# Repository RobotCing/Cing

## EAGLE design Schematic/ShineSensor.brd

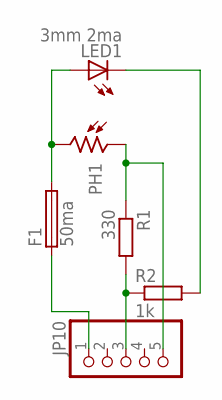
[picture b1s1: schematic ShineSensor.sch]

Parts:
F1: 50ma; MF-SMDF050
JP10: PINHD-1X5; 1X05
LED1: 3mm 2ma; LED3MM
PH1: B1060_23; TO-8_B10
R1: 330; R1206
R2: 1k; R1206

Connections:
unnamed: F1.2, LED1.A, PH1.2
unnamed: LED1.K (C), R2.2
unnamed: JP10.5, PH1.1, R1.1
unnamed: JP10.3, R1.2, R2.1
unnamed: F1.1, JP10.1

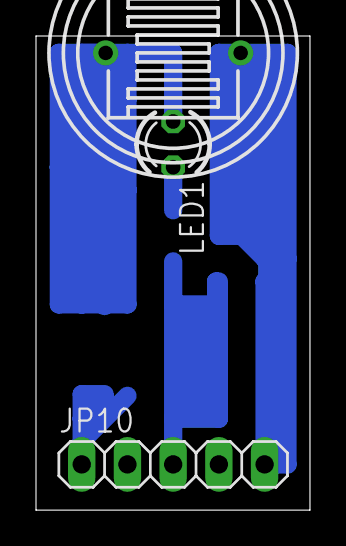
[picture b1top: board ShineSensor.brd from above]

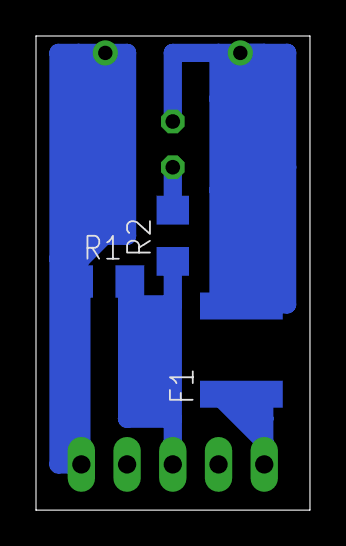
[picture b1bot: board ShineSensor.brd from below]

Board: 2 copper layers, 15.2 x 26.3 mm, 6 parts (3 on the bottom side), 5 nets.

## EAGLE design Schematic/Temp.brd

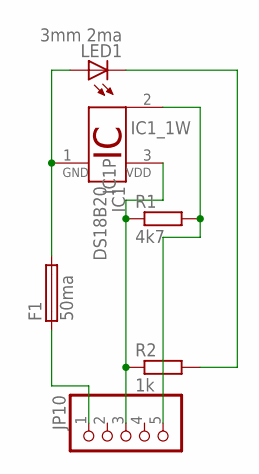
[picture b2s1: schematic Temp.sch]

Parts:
F1: 50ma; MF-SMDF050
IC1: DS18B20; TO92-
JP10: PINHD-1X5; 1X05
LED1: 3mm 2ma; LED3MM
R1: 4k7; R1206
R2: 1k; R1206

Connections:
unnamed: F1.2, IC1.1 (GND), LED1.A
unnamed: LED1.K (C), R2.2
unnamed: IC1.2 (1W), JP10.5, R1.2
unnamed: IC1.3 (VDD), JP10.3, R1.1, R2.1
unnamed: F1.1, JP10.1

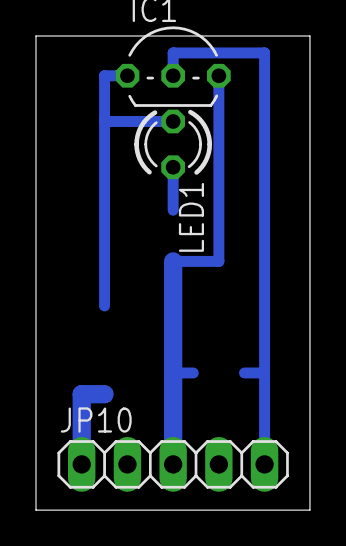
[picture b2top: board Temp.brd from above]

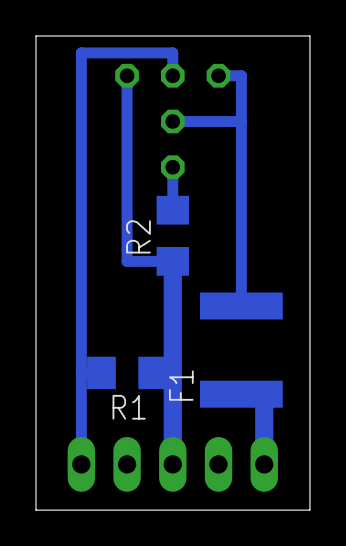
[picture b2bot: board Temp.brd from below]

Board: 2 copper layers, 15.2 x 26.3 mm, 6 parts (3 on the bottom side), 5 nets.

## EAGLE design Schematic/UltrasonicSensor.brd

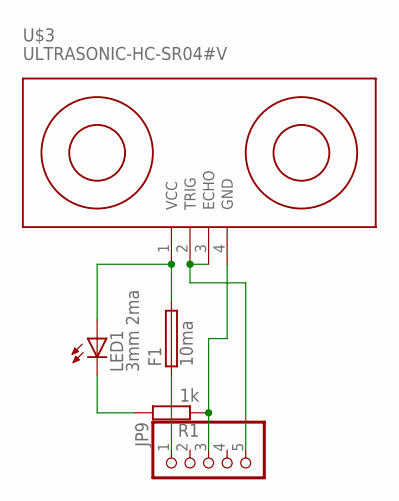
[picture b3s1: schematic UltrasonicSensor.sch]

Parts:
F1: 10ma; MF-SMDF050
JP9: PINHD-1X5; 1X05
LED1: 3mm 2ma; LED3MM
R1: 1k; M1206
U$3: ULTRASONIC-HC-SR04#V

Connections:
unnamed: JP9.3, R1.1, U$3.4 (GND)
unnamed: F1.1, JP9.1
unnamed: F1.2, LED1.A, U$3.1 (VCC)
unnamed: LED1.K (C), R1.2
unnamed: JP9.5, U$3.2 (TRIG), U$3.3 (ECHO)

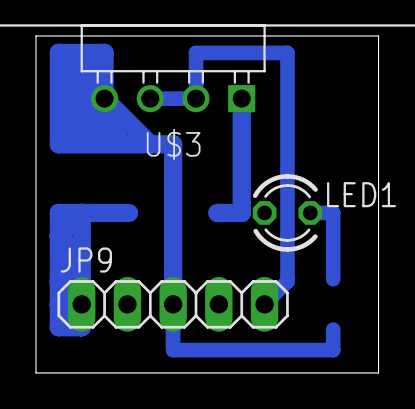
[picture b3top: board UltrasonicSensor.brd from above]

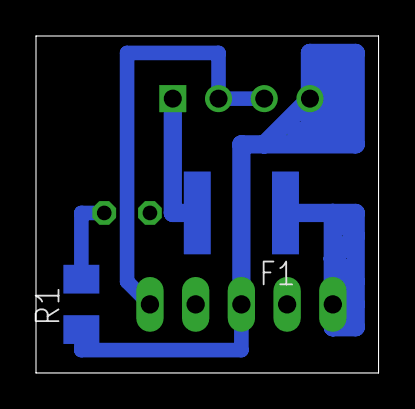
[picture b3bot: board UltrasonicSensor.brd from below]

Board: 2 copper layers, 19.0 x 18.7 mm, 5 parts (2 on the bottom side), 5 nets.

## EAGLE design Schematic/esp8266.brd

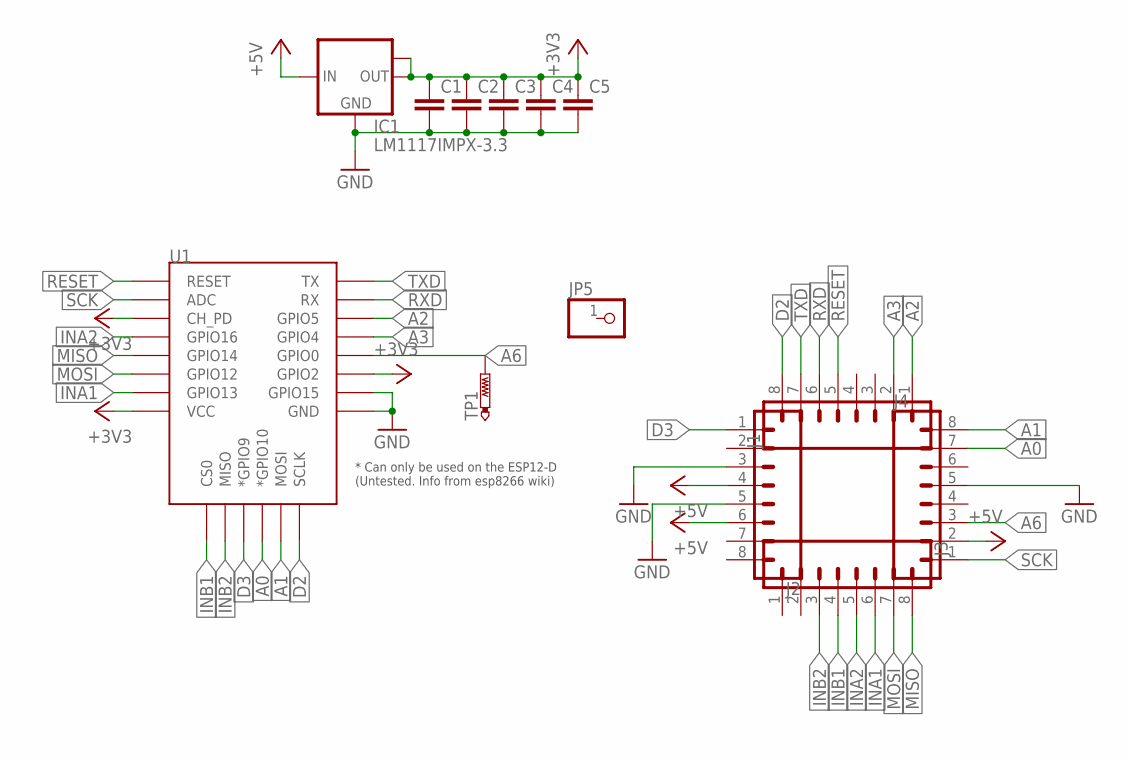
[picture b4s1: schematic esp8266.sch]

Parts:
C1, C2, C3, C4, C5: C-EUC1206K; C1206K
IC1: LM1117IMPX-3.3; SOT223
J1, J2, J3, J4: CONN_08SMD-STRAIGHT-ALT-FEMALE; 1X08_SMD_ALT
JP5: PINHD-1X1; 1X01
TP1: PTR1B1,27; B1,27
U1: ESP12ESMD; ESP12E-SMD

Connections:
+3V3: C1.1, C2.1, C3.1, C4.1, C5.1, IC1.2 (OUT), IC1.TAB (OUT1), U1.CH_PD, U1.GPIO2, U1.VCC
+5V: IC1.3 (IN), J2.4, J2.6, J4.2
A0: J4.7, U1.GPIO10 (*GPIO10)
A1: J4.8, U1.MOSI
A2: J1.1, U1.GPIO5
A3: J1.2, U1.GPIO4
A6: J4.3, TP1.TP, U1.GPIO0
D2: J1.8, U1.SCLK
D3: J2.1, U1.GPIO9 (*GPIO9)
GND: C1.2, C2.2, C3.2, C4.2, C5.2, IC1.1 (GND), J2.3, J2.5, J4.5, U1.GND, U1.GPIO15
INA1: J3.6, U1.GPIO13
INA2: J3.5, U1.GPIO16
INB1: J3.4, U1.CS0
INB2: J3.3, U1.MISO
MISO: J3.8, U1.GPIO14
MOSI: J3.7, U1.GPIO12
RESET: J1.5, U1.RESET
RXD: J1.6, U1.RXD0 (RX)
SCK: J4.1, U1.ADC
TXD: J1.7, U1.TXD0 (TX)

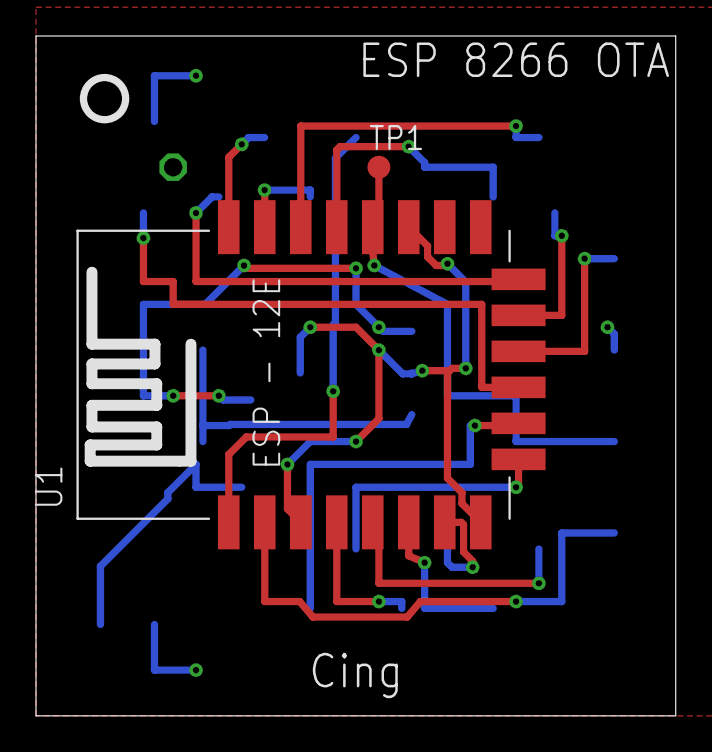
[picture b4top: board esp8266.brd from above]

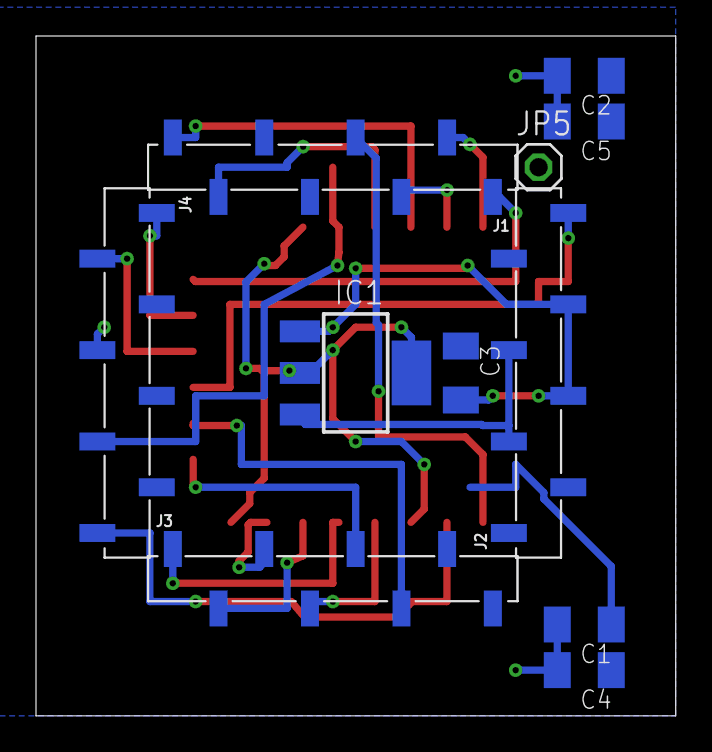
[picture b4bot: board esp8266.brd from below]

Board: 2 copper layers, 35.5 x 37.8 mm, 13 parts (11 on the bottom side), 20 nets.

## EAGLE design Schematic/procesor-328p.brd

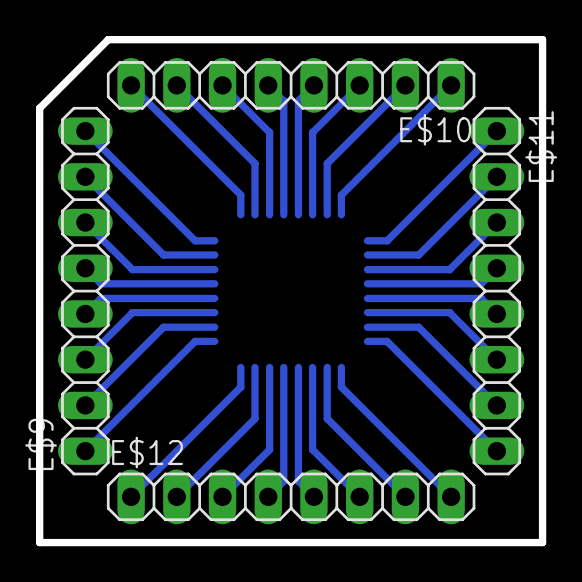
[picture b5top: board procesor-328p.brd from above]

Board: 2 copper layers, 27.9 x 27.9 mm, 5 parts (1 on the bottom side), 32 nets.

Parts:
ATMEGA328P: QFP80P900X900X120-32N
E$9, E$10, E$11, E$12: 1X08

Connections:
S$1: ATMEGA328P.1, E$10.8
S$2: ATMEGA328P.2, E$10.7
S$3: ATMEGA328P.3, E$10.6
S$4: ATMEGA328P.4, E$10.5
S$5: ATMEGA328P.5, E$10.4
S$6: ATMEGA328P.6, E$10.3
S$7: ATMEGA328P.7, E$10.2
S$8: ATMEGA328P.8, E$10.1
S$9: ATMEGA328P.9, E$11.1
S$10: ATMEGA328P.10, E$11.2
S$11: ATMEGA328P.11, E$11.3
S$12: ATMEGA328P.12, E$11.4
S$13: ATMEGA328P.13, E$11.5
S$14: ATMEGA328P.14, E$11.6
S$15: ATMEGA328P.15, E$11.7
S$16: ATMEGA328P.16, E$11.8
S$17: ATMEGA328P.17, E$12.8
S$18: ATMEGA328P.18, E$12.7
S$19: ATMEGA328P.19, E$12.6
S$20: ATMEGA328P.20, E$12.5
S$21: ATMEGA328P.21, E$12.4
S$22: ATMEGA328P.22, E$12.3
S$23: ATMEGA328P.23, E$12.2
S$24: ATMEGA328P.24, E$12.1
S$25: ATMEGA328P.25, E$9.1
S$26: ATMEGA328P.26, E$9.2
S$27: ATMEGA328P.27, E$9.3
S$28: ATMEGA328P.28, E$9.4
S$29: ATMEGA328P.29, E$9.5
S$30: ATMEGA328P.30, E$9.6
S$31: ATMEGA328P.31, E$9.7
S$32: ATMEGA328P.32, E$9.8

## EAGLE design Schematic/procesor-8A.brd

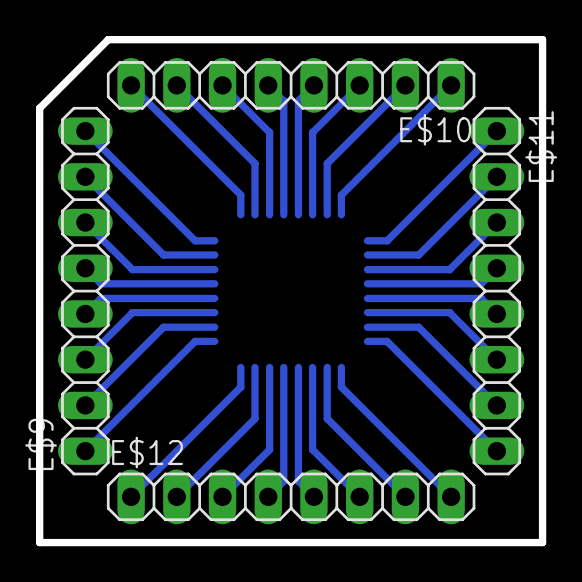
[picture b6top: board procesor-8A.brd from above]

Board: 2 copper layers, 27.9 x 27.9 mm, 5 parts (1 on the bottom side), 32 nets.

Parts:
ATMEGA8A: QFP80P900X900X120-32N
E$9, E$10, E$11, E$12: 1X08

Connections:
S$1: ATMEGA8A.1, E$10.8
S$2: ATMEGA8A.2, E$10.7
S$3: ATMEGA8A.3, E$10.6
S$4: ATMEGA8A.4, E$10.5
S$5: ATMEGA8A.5, E$10.4
S$6: ATMEGA8A.6, E$10.3
S$7: ATMEGA8A.7, E$10.2
S$8: ATMEGA8A.8, E$10.1
S$9: ATMEGA8A.9, E$11.1
S$10: ATMEGA8A.10, E$11.2
S$11: ATMEGA8A.11, E$11.3
S$12: ATMEGA8A.12, E$11.4
S$13: ATMEGA8A.13, E$11.5
S$14: ATMEGA8A.14, E$11.6
S$15: ATMEGA8A.15, E$11.7
S$16: ATMEGA8A.16, E$11.8
S$17: ATMEGA8A.17, E$12.8
S$18: ATMEGA8A.18, E$12.7
S$19: ATMEGA8A.19, E$12.6
S$20: ATMEGA8A.20, E$12.5
S$21: ATMEGA8A.21, E$12.4
S$22: ATMEGA8A.22, E$12.3
S$23: ATMEGA8A.23, E$12.2
S$24: ATMEGA8A.24, E$12.1
S$25: ATMEGA8A.25, E$9.1
S$26: ATMEGA8A.26, E$9.2
S$27: ATMEGA8A.27, E$9.3
S$28: ATMEGA8A.28, E$9.4
S$29: ATMEGA8A.29, E$9.5
S$30: ATMEGA8A.30, E$9.6
S$31: ATMEGA8A.31, E$9.7
S$32: ATMEGA8A.32, E$9.8

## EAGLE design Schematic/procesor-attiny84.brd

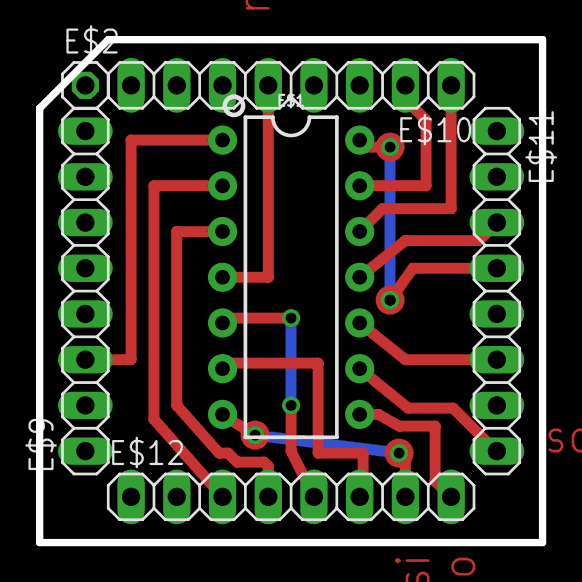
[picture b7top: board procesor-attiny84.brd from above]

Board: 2 copper layers, 27.9 x 27.9 mm, 6 parts (0 on the bottom side), 14 nets.

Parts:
E$1: DIP14
E$2: 1X01
E$9, E$10, E$11, E$12: 1X08

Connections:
S$2: E$1.4, E$10.5
S$3: E$1.14, E$11.4
S$4: E$1.1, E$9.3
S$5: E$1.9, E$11.8
S$6: E$1.12, E$10.1
S$7: E$1.13, E$10.2
S$8: E$1.7, E$12.7
S$10: E$1.8, E$12.8
S$11: E$1.10, E$11.6
S$12: E$1.11, E$11.3
S$13: E$1.2, E$12.3
S$14: E$1.3, E$12.4
S$15: E$1.5, E$12.5
S$18: E$1.6, E$12.6

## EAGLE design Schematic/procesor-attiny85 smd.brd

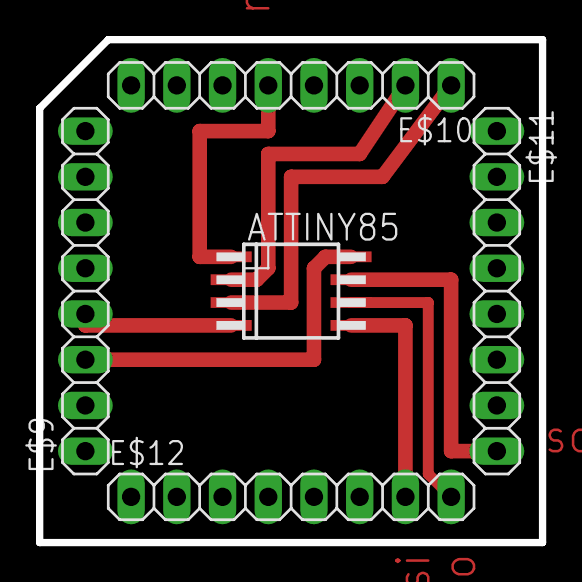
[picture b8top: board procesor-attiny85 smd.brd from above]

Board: 2 copper layers, 27.9 x 27.9 mm, 5 parts (0 on the bottom side), 8 nets.

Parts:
ATTINY85: ATTINY85
E$9, E$10, E$11, E$12: 1X08

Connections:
S$2: ATTINY85.1, E$10.5
S$3: ATTINY85.4, E$9.4
S$4: ATTINY85.8, E$9.3
S$5: ATTINY85.7, E$11.8
S$6: ATTINY85.3, E$10.1
S$7: ATTINY85.2, E$10.2
S$8: ATTINY85.5, E$12.7
S$10: ATTINY85.6, E$12.8

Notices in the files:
parts and their libraries:
diy-modules: Released under the Creative Commons Attribution 4.0 International License: http://creativecommons.org/licenses/by/4.0
SparkFun-Connectors: Licensing: Creative Commons ShareAlike 4.0 International - https://creativecommons.org/licenses/by-sa/4.0
